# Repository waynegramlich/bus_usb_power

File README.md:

# bus_usb_power
Bus Power Board with USB Power Outputs

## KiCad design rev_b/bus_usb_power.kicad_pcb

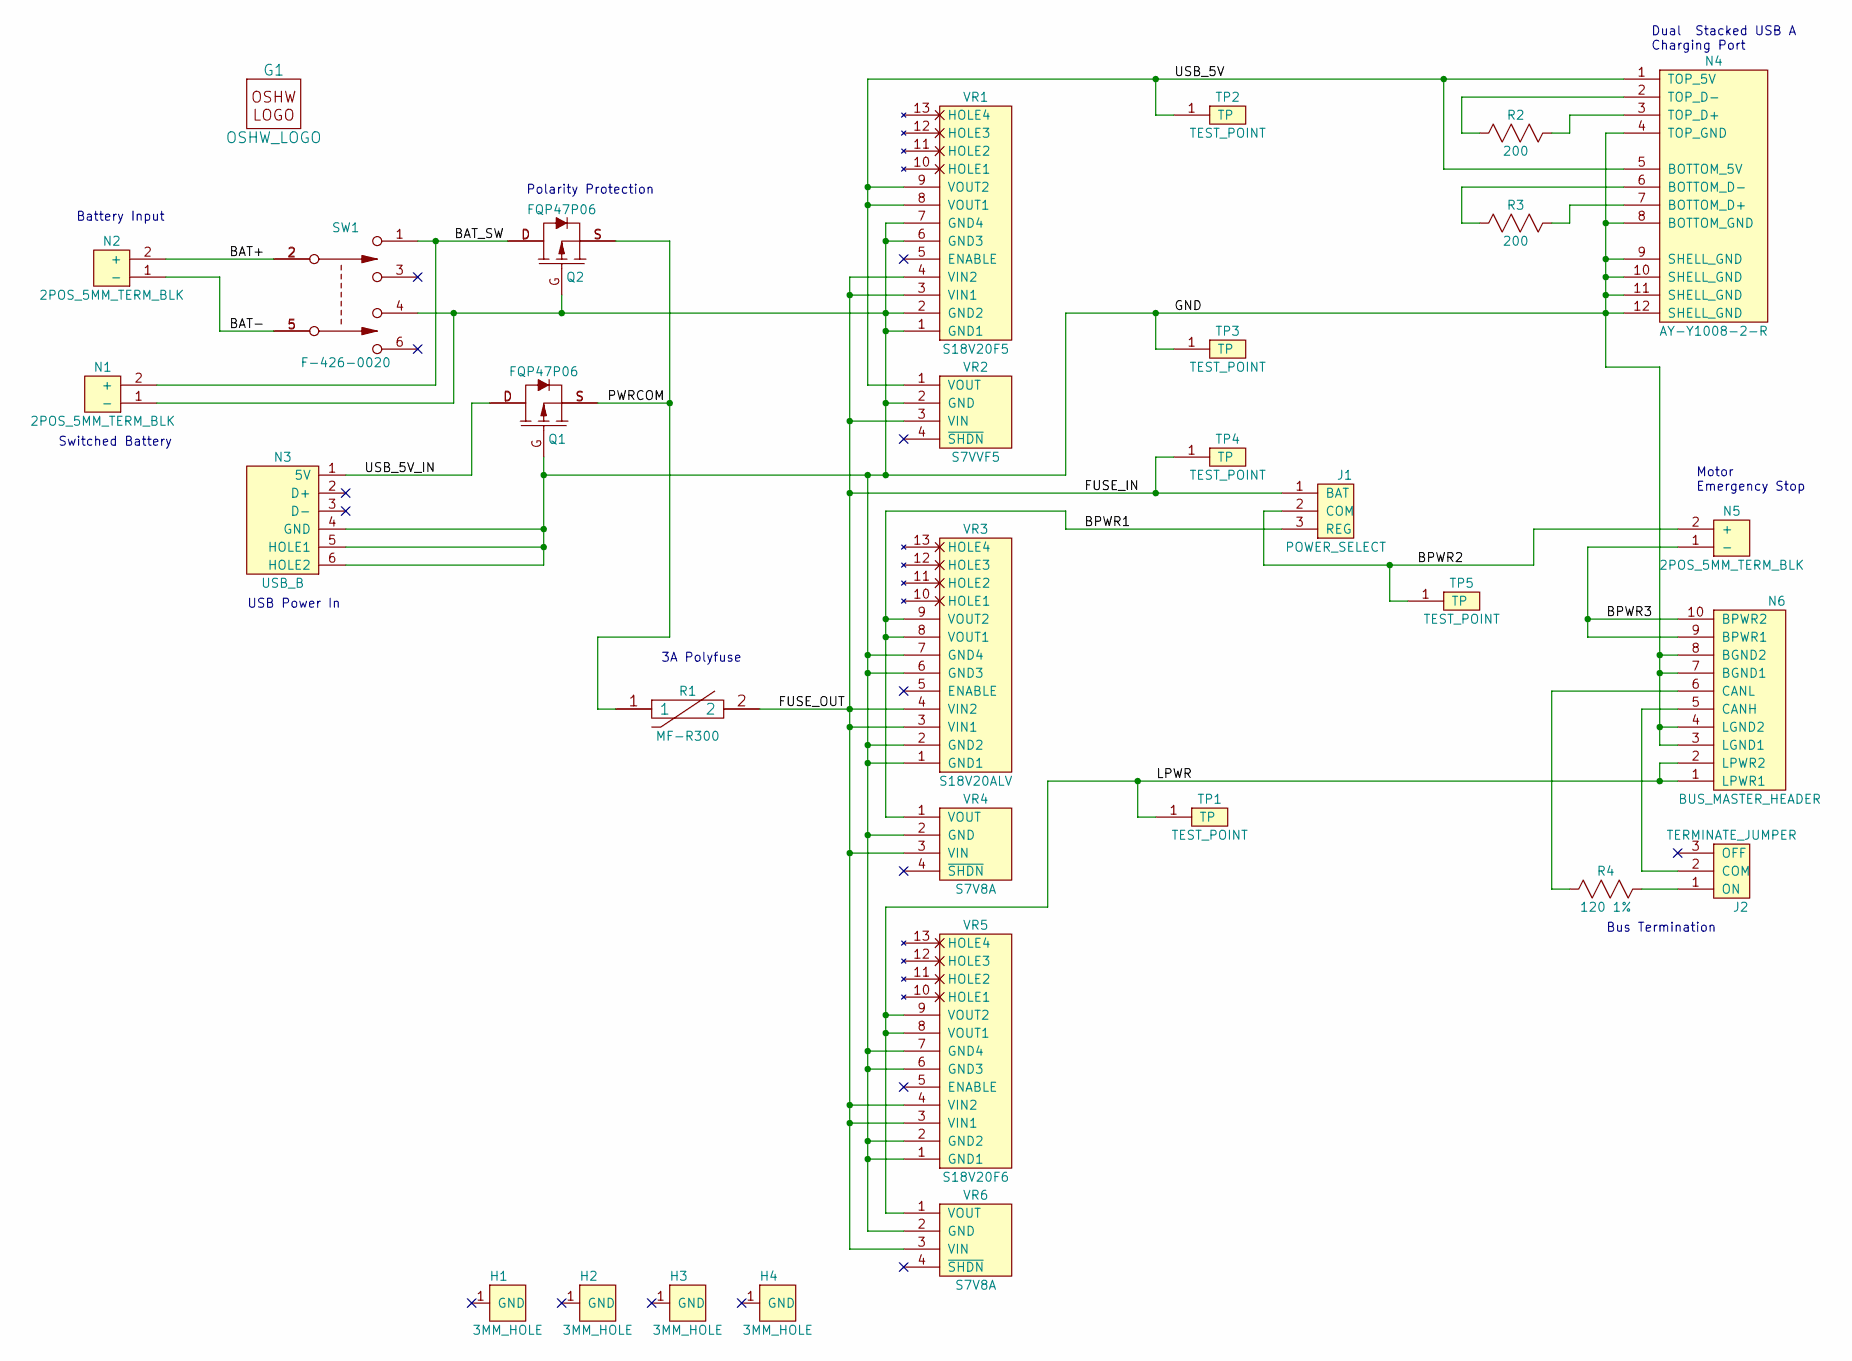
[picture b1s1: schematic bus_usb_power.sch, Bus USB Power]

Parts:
G1: OSHW_LOGO; OSHW_LOGO_400mil
H1, H2, H3, H4: 3MM_HOLE; MountingHole_3mm
J1: POWER_SELECT; Pin_Header_Straight_1x03
J2: TERMINATE_JUMPER; Pin_Header_Straight_1x03
N1, N2, N5: 2POS_5MM_TERM_BLK; 5MM_TERMINAL_BLOCK_2_POS
N3: USB_B
N4: AY-Y1008-2-R; DUAL_USB_A
N6: BUS_MASTER_HEADER; Pin_Header_Straight_2x05_Shrouded
Q1, Q2: FQP47P06; TO-220_FET-GDS_Horizontal_LargePads
R1: MF-R300; MF_R300
R2, R3: 200; Resistor_Horizontal_400
R4: 120 1%; Resistor_Horizontal_400
SW1: F-426-0020; GF_426_0020
TP1, TP2, TP3, TP4, TP5: TEST_POINT; Pin_Header_Straight_1x01
VR1: S18V20F5; S18V20Fx
VR2: S7VVF5; Pin_Header_Straight_1x04
VR3: S18V20ALV; S18V20Fx
VR4, VR6: S7V8A; Pin_Header_Straight_1x04
VR5: S18V20F6; S18V20Fx

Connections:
/BAT+: N2.2 (+), SW1.2
/BAT-: N2.1 (-), SW1.5
/BAT_SW: N1.2 (+), Q2.D, SW1.1
/BPWR1: J1.3 (REG), VR3.8 (VOUT1), VR3.9 (VOUT2), VR4.1 (VOUT)
/BPWR2: J1.2 (COM), N5.2 (+), TP5.1
/BPWR3: N5.1 (-), N6.9 (BPWR1), N6.10 (BPWR2)
/FUSE_IN: J1.1 (BAT), R1.2, TP4.1, VR1.3 (VIN1), VR1.4 (VIN2), VR2.3 (VIN), VR3.3 (VIN1), VR3.4 (VIN2), VR4.3 (VIN), VR5.3 (VIN1), VR5.4 (VIN2), VR6.3 (VIN)
/GND: N1.1 (-), N3.4 (GND), N3.5 (HOLE1), N3.6 (HOLE2), N4.4 (TOP_GND), N4.8 (BOTTOM_GND), N4.9 (SHELL_GND), N4.10 (SHELL_GND), N4.11 (SHELL_GND), N4.12 (SHELL_GND), N6.3 (LGND1), N6.4 (LGND2), N6.7 (BGND1), N6.8 (BGND2), Q1.G, Q2.G, SW1.4, TP3.1, VR1.1 (GND1), VR1.2 (GND2), VR1.6 (GND3), VR1.7 (GND4), VR2.2 (GND), VR3.1 (GND1), VR3.2 (GND2), VR3.6 (GND3), VR3.7 (GND4), VR4.2 (GND), VR5.1 (GND1), VR5.2 (GND2), VR5.6 (GND3), VR5.7 (GND4), VR6.2 (GND)
/LPWR: N6.1 (LPWR1), N6.2 (LPWR2), TP1.1, VR5.8 (VOUT1), VR5.9 (VOUT2), VR6.1 (VOUT)
/PWRCOM: Q1.S, Q2.S, R1.1
/USB_5V: N4.1 (TOP_5V), N4.5 (BOTTOM_5V), TP2.1, VR1.8 (VOUT1), VR1.9 (VOUT2), VR2.1 (VOUT)
/USB_5V_IN: N3.1 (5V), Q1.D
unnamed: J2.1 (ON), R4.2
unnamed: J2.2 (COM), N6.5 (CANH)
unnamed: N4.2 (TOP_D-), R2.1
unnamed: N4.3 (TOP_D+), R2.2
unnamed: N4.6 (BOTTOM_D-), R3.1
unnamed: N4.7 (BOTTOM_D+), R3.2
unnamed: N6.6 (CANL), R4.1

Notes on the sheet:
Switched Battery
Motor Emergency Stop
Battery Input
3A Polyfuse
Polarity Protection
Dual Stacked USB A Charging Port
Bus Termination
USB Power In

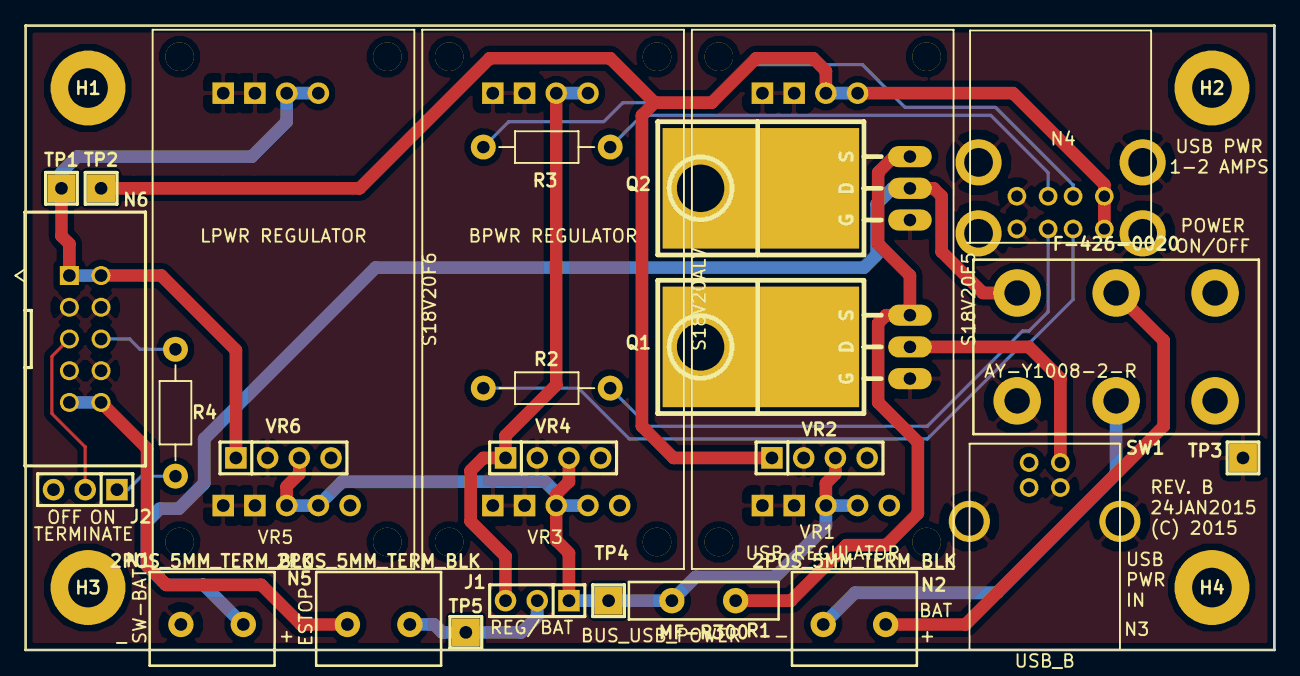
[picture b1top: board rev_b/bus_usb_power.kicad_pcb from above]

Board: 2 copper layers, 100.0 x 50.0 mm, 31 parts (1 on the bottom side), 19 nets.

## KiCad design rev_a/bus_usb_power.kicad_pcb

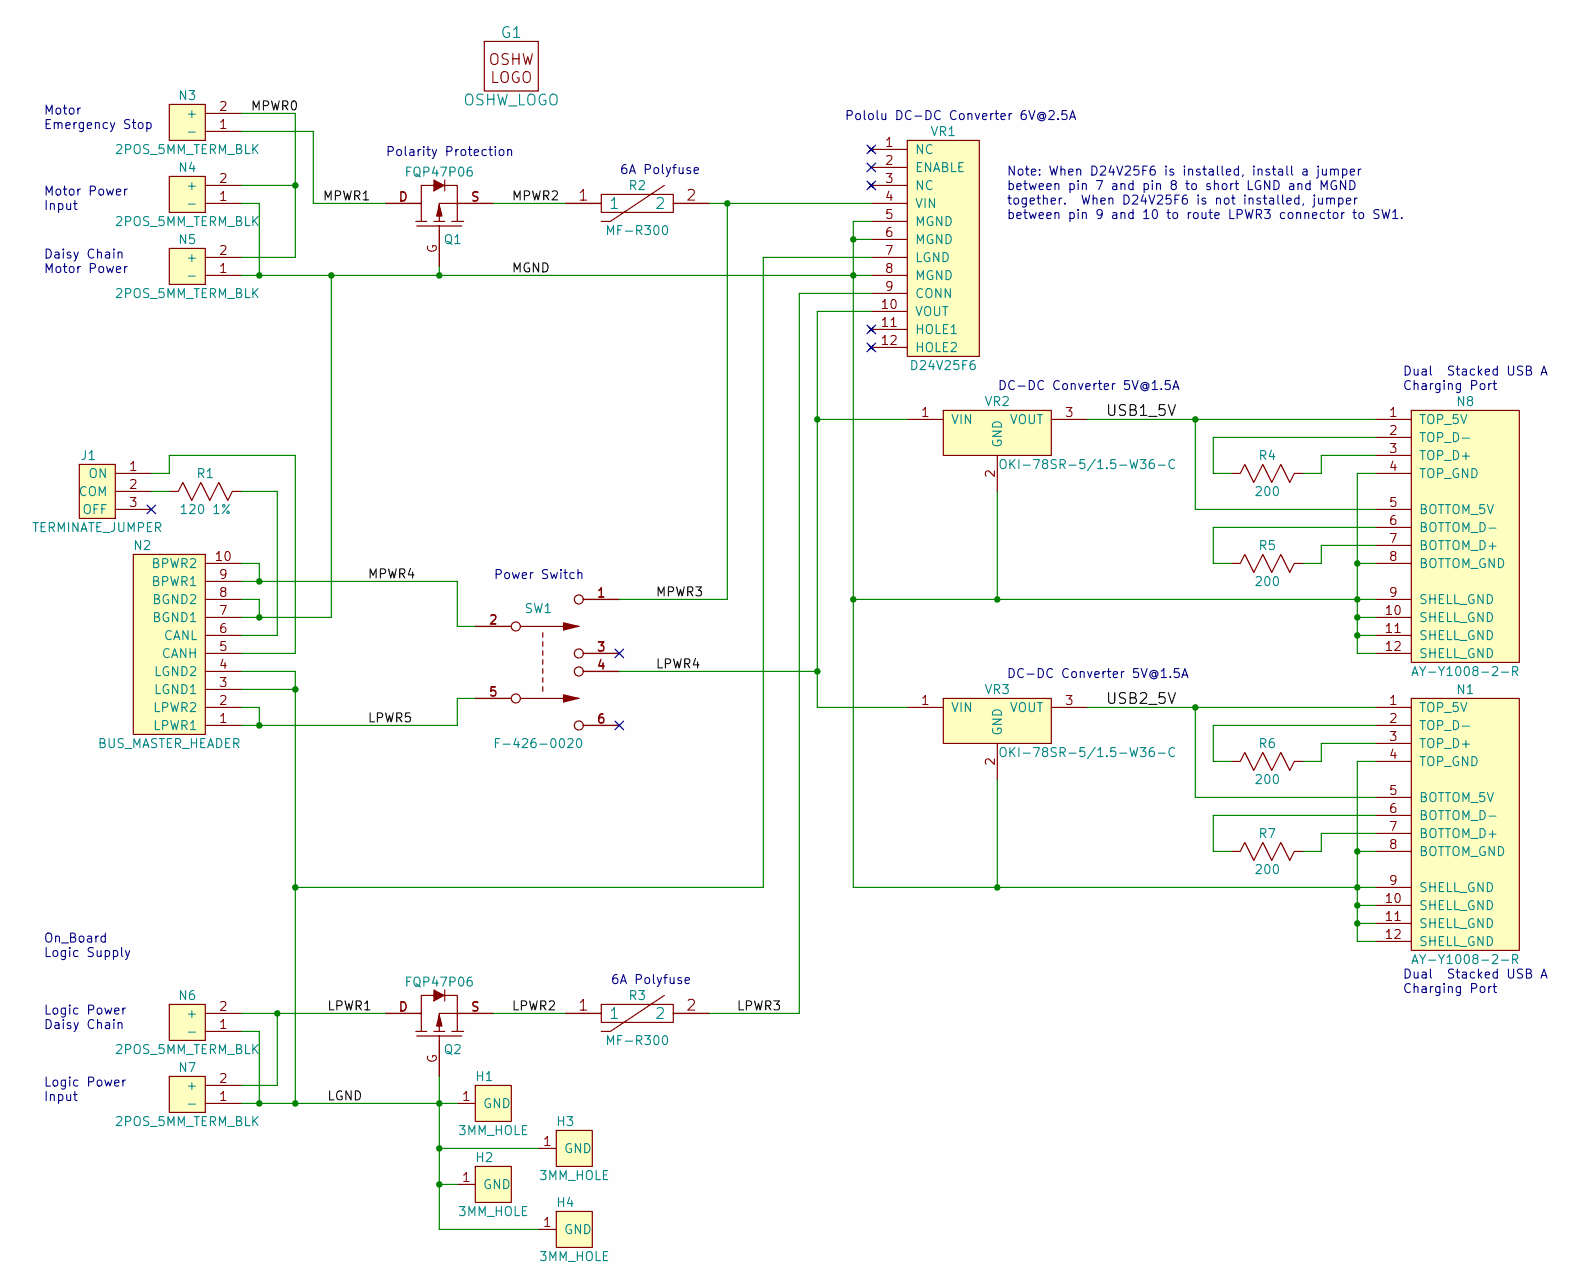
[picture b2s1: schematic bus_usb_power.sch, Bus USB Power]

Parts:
G1: OSHW_LOGO; OSHW_LOGO_400mil
H1, H2, H3, H4: 3MM_HOLE; MountingHole_3mm
J1: TERMINATE_JUMPER; Pin_Header_Straight_1x03
N1, N8: AY-Y1008-2-R; DUAL_USB_A
N2: BUS_MASTER_HEADER; Pin_Header_Straight_2x05_Shrouded
N3, N4, N5, N6, N7: 2POS_5MM_TERM_BLK; 5MM_TERMINAL_BLOCK_2_POS
Q1, Q2: FQP47P06; TO-220_FET-GDS_Horizontal_LargePads
R1: 120 1%; Resistor_Horizontal_400
R2, R3: MF-R300; MF_R300
R4, R5, R6, R7: 200; Resistor_Horizontal_400
SW1: F-426-0020; GF_426_0020
VR1: D24V25F6
VR2: OKI-78SR-5/1.5-W36-C
VR3: OKI-78SR-5/1.5-W36-C

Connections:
/LGND: H1.1, H2.1, H3.1, H4.1, N2.3 (LGND1), N2.4 (LGND2), N6.1 (-), N7.1 (-), Q2.G, VR1.7 (LGND)
/LPWR1: N6.2 (+), N7.2 (+), Q2.D
/LPWR2: Q2.S, R3.1
/LPWR3: R3.2, VR1.9 (CONN)
/LPWR4: SW1.4, VR1.10 (VOUT), VR2.1 (VIN), VR3.1 (VIN)
/LPWR5: N2.1 (LPWR1), N2.2 (LPWR2), SW1.5
/MGND: N1.4 (TOP_GND), N1.8 (BOTTOM_GND), N1.9 (SHELL_GND), N1.10 (SHELL_GND), N1.11 (SHELL_GND), N1.12 (SHELL_GND), N2.7 (BGND1), N2.8 (BGND2), N4.1 (-), N5.1 (-), N8.4 (TOP_GND), N8.8 (BOTTOM_GND), N8.9 (SHELL_GND), N8.10 (SHELL_GND), N8.11 (SHELL_GND), N8.12 (SHELL_GND), Q1.G, VR1.5 (MGND), VR1.6 (MGND), VR1.8 (MGND), VR2.2 (GND), VR3.2 (GND)
/MPWR0: N3.2 (+), N4.2 (+), N5.2 (+)
/MPWR1: N3.1 (-), Q1.D
/MPWR2: Q1.S, R2.1
/MPWR3: R2.2, SW1.1, VR1.4 (VIN)
/MPWR4: N2.9 (BPWR1), N2.10 (BPWR2), SW1.2
/USB1_5V: N8.1 (TOP_5V), N8.5 (BOTTOM_5V), VR2.3 (VOUT)
/USB2_5V: N1.1 (TOP_5V), N1.5 (BOTTOM_5V), VR3.3 (VOUT)
unnamed: J1.1 (ON), N2.5 (CANH)
unnamed: J1.2 (COM), R1.1
unnamed: N1.2 (TOP_D-), R6.1
unnamed: N1.3 (TOP_D+), R6.2
unnamed: N1.6 (BOTTOM_D-), R7.1
unnamed: N1.7 (BOTTOM_D+), R7.2
unnamed: N2.6 (CANL), R1.2
unnamed: N8.2 (TOP_D-), R4.1
unnamed: N8.3 (TOP_D+), R4.2
unnamed: N8.6 (BOTTOM_D-), R5.1
unnamed: N8.7 (BOTTOM_D+), R5.2

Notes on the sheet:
Daisy Chain Motor Power
Motor Emergency Stop
Logic Power Input
Motor Power Input
Logic Power Daisy Chain
DC-DC Converter 5V@1.5A
Pololu DC-DC Converter 6V@2.5A
6A Polyfuse
Polarity Protection
Dual Stacked USB A Charging Port
On_Board Logic Supply
Note: When D24V25F6 is installed, install a jumper between pin 7 and pin 8 to short LGND and MGND together. When D24V25F6 is not installed, jumper between pin 9 and 10 to route LPWR3 connector to SW1.
Power Switch

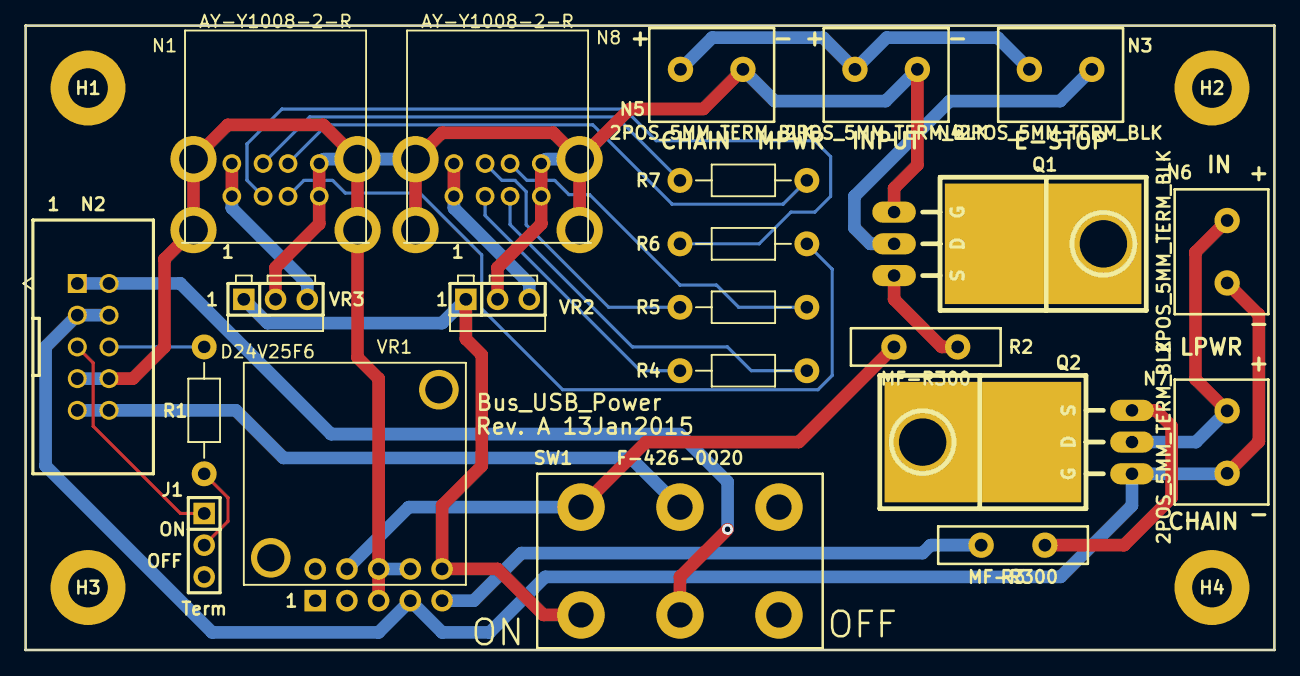
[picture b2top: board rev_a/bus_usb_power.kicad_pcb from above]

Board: 2 copper layers, 100.0 x 50.0 mm, 27 parts (1 on the bottom side), 25 nets.

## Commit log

2015-01-09 Made a copy of bus_power Rev. B.
2015-01-09 Renamed everything from bus_power to bus_usb_power.
2015-01-09 Changed internal references from bus_power to bus_usb_power.
2015-01-10 Initial layout of Rev. A is complete.
2015-01-13 Rev A. read for manufacture.
2015-01-21 Copied rev_a over to rev_b
2015-01-21 Fixed a whole bunch of issues.
2015-01-24 Mid-point to a fairly major change.
2015-01-24 Rev. B is looking pretty good.
2015-01-25 More fine tuning of Rev. B

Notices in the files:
rev_b/bus_usb_power.kicad_pcb:
Copyright (c) 2015
(C) 2015
